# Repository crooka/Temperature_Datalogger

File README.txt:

Reach out to andrew.crook@usu.edu with any questions. 

Use 1 Oz copper
Green soldermask preferred

Most parts have links to both Digikey and JLCPCB. JLCPCB is the preferred supplier, but the big capacitors will need to come from digikey. 
UPDATE: due to cost, I'm only getting the top side assembled, and I'm not getting the ESP32 put on because that will drive up cost. Planning to put the ESP32 with solder paste and the reflow oven at work, and hand solder the back side. 

This section is so I can keep track of what's for what. 
Component purpose/notes:

R11,R12: 	Tell usb to send over 5V
C11,C13,C14,C15:Clean up power to sensors and some ESD protection
C7,C3,C6,C5: 	Clean up power from AMS1117
AMS1117: 	Linear voltage regulator to convert 5V to 3.3V (This is isn't as efficient as a buck converter)
D1: 		Probably not necessary, but this is back current protection. It was in the example. 
R5,R8:		Pull up resistors for the buttons

ESP32: 		This is the brains. Pushing the enable button should reset the board, The IO0 button should make it enter boot mode. 

TMP117: Maybe add in a zero ohm resistor option later so gpio16 can be used for either temperature interrupts or broken out for general IO depending on the assembly? 
	Verify that tying ADD0 to GND gives I2C address 0x48.
	Using recommended 4.7Kohm pull up resistor for SDA and SCL. One source said 2.2K may be better?  

BH1750: Tie ADDR to GND for I2C address 0x23

BME280 Tie CSB to VDDIO for I2C (tie to GND for SPI) With I2C selected, tie SDO to GND for I2C address 0x76

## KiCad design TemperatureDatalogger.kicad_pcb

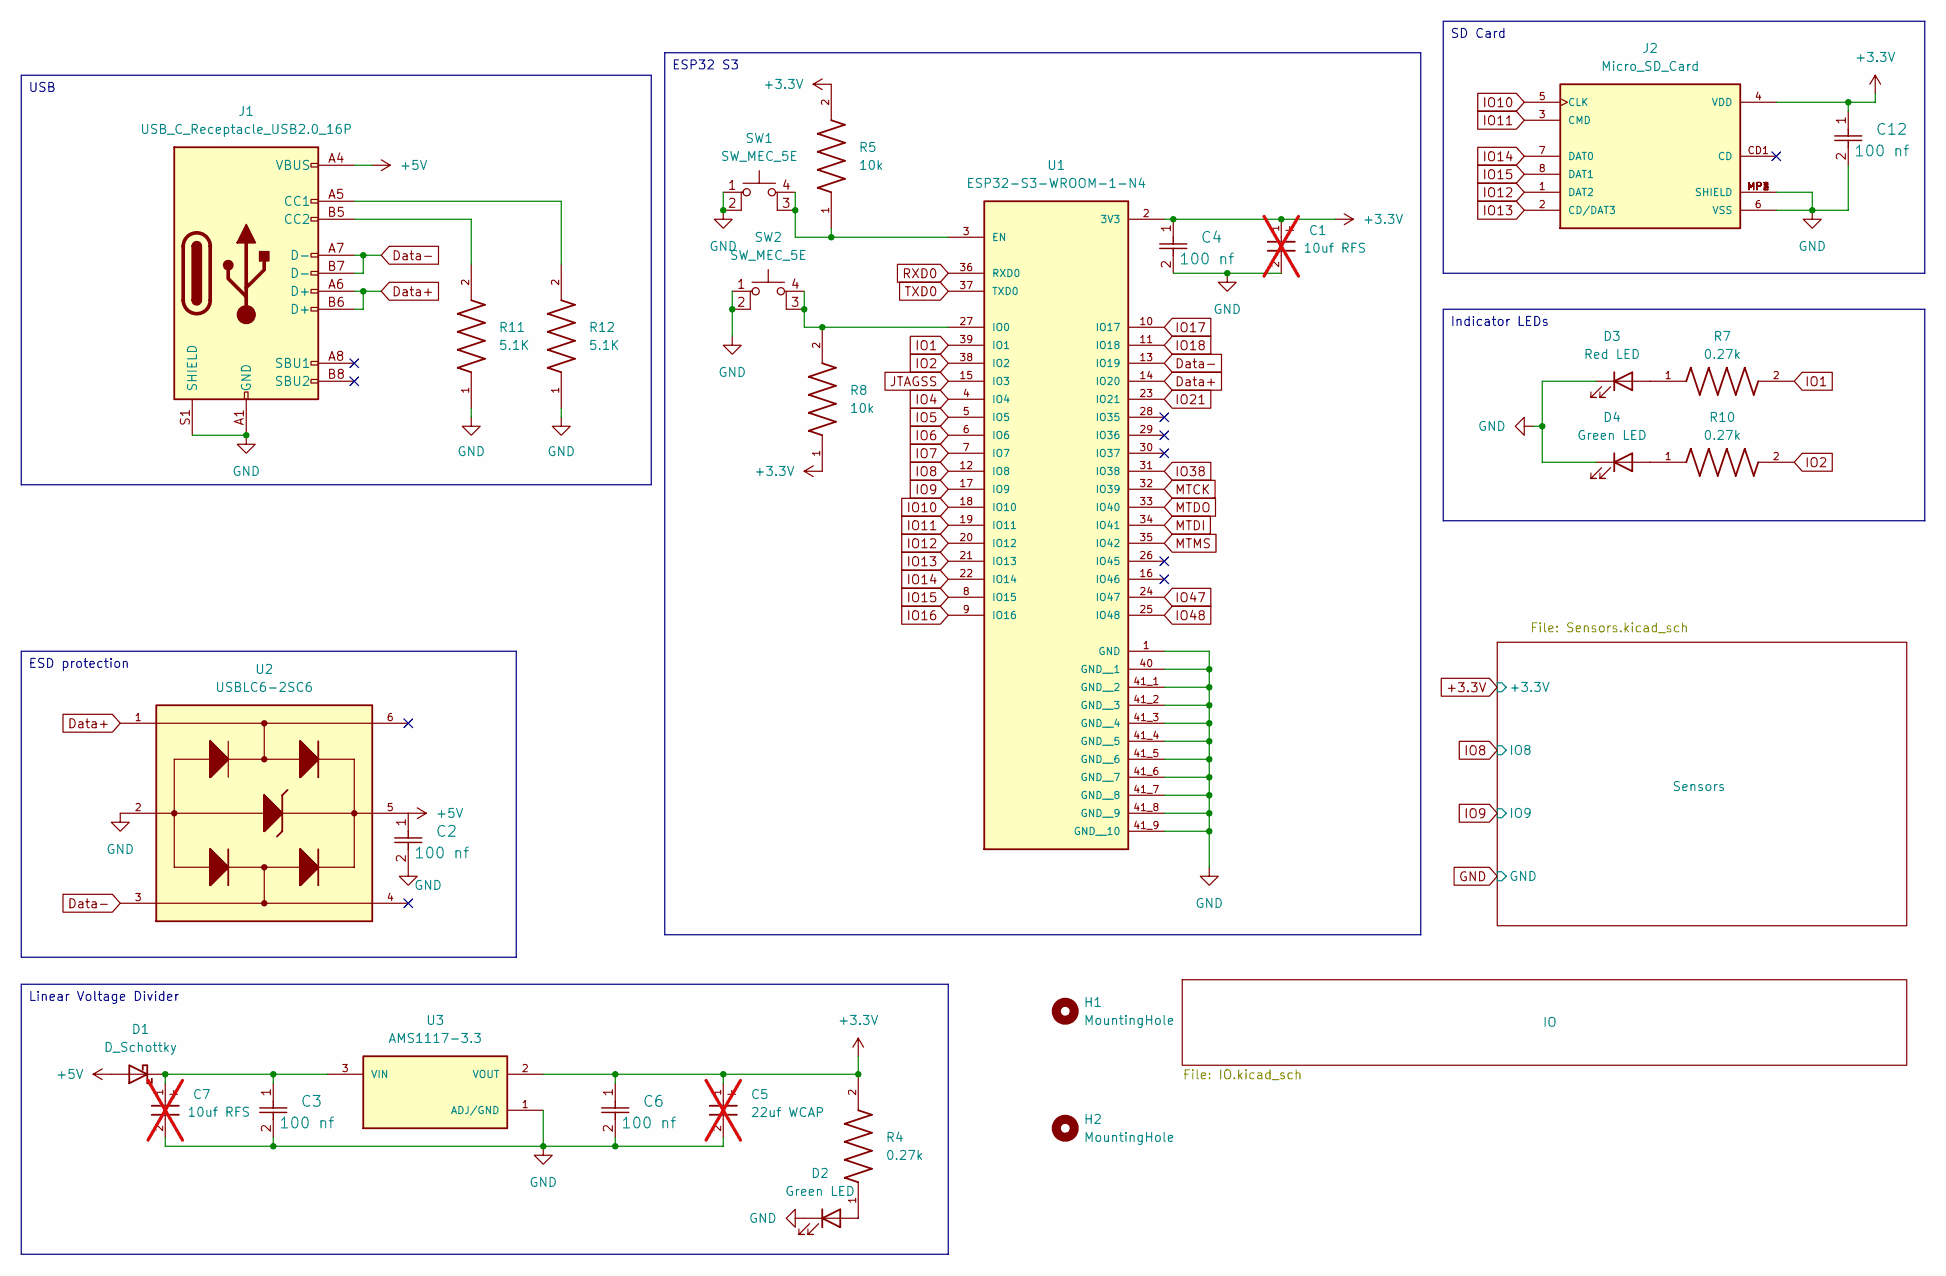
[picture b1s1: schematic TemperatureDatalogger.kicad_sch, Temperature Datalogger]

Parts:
C1, C7: 10uf RFS; RF-A_NCH-M; MPN RFS1A100MCN1GB; not fitted
C2, C3, C4, C6, C12: 100 nf; CAP_CC0603KRX5R8BB104_YAG-M; MPN CC0603KRX5R8BB104
C5: 22uf WCAP; WCAP-PSLP_4X5.5_DXL_; MPN 875105240003; not fitted
D1: D_Schottky; DO-214AC_VIS-M; MPN BYS10-25-E3/TR
D2, D4: Green LED; LED_0604_SMD; MPN 150060VS55040
D3: Red LED; LED_0604_SMD; MPN 150060RS75000
H1, H2: MountingHole; MountingHole_2.7mm_M2.5_ISO14580
J1: USB_C_Receptacle_USB2.0_16P; USB_C_Receptacle_HRO_TYPE-C-31-M-12; MPN TYPE-C-31-M-12
J2: Micro_SD_Card; TF-01A; MPN TF-01A
R4, R7, R10: 0.27k; RES_ERJPA3F2700V; MPN RC0603FR-13270RL
R5, R8: 10k; RES_ERJPA3F2700V; MPN RC0603FR-0710KL
R11, R12: 5.1K; RES_ERJPA3F2700V; MPN RC0603FR-075K1L
SW1, SW2: SW_MEC_5E; button; MPN B3SN-3012P
U1: ESP32-S3-WROOM-1-N4; XCVR_ESP32-S3-WROOM-1-N4; PARTREV v1.0
U2: USBLC6-2SC6; SOT95P280X145-6N; MPN USBLC6-2SC6
U3: AMS1117-3.3; SOT229P700X180-4N; PARTREV NA

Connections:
+3.3V: C1.1, C4.1, C5.1, C6.1, C12.1, J2.4 (VDD), R4.2, R5.2, R8.1, U1.2 (3V3), U3.2 (VOUT); also elsewhere on the board
+5V: C2.1, D1.2 (A), J1.A4 (VBUS), J1.A9 (VBUS), J1.B4 (VBUS), J1.B9 (VBUS), U2.5; also elsewhere on the board
Data+: J1.A6 (D+), J1.B6 (D+), U1.14 (IO20), U2.1
Data-: J1.A7 (D-), J1.B7 (D-), U1.13 (IO19), U2.3
GND: C1.2, C2.2, C3.2, C4.2, C5.2, C6.2, C7.2, C12.2, D2.1 (K), D3.1 (K), D4.1 (K), J1.A1 (GND), J1.A12 (GND), J1.B1 (GND), J1.B12 (GND), J1.S1 (SHIELD), J2.6 (VSS), J2.MP1 (SHIELD), J2.MP2 (SHIELD), J2.MP3 (SHIELD), J2.MP4 (SHIELD), R11.1, R12.1, SW1.1, SW1.2, SW2.1, SW2.2, U1.1 (GND), U1.40 (GND__1), U1.41_1 (GND__2), U1.41_2 (GND__3), U1.41_3 (GND__4), U1.41_4 (GND__5), U1.41_5 (GND__6), U1.41_6 (GND__7), U1.41_7 (GND__8), U1.41_8 (GND__9), U1.41_9 (GND__10), U1.41_10, U1.41_11, U1.41_12, U1.41_13, U1.41_14, U1.41_15, U1.41_16, U1.41_17, U1.41_18, U1.41_19, U1.41_20, U1.41_21, U2.2, U3.1 (ADJ/GND); also elsewhere on the board
IO1: R7.2, U1.39 (IO1)
IO2: R10.2, U1.38 (IO2)
IO4: U1.4 (IO4); also elsewhere on the board
IO5: U1.5 (IO5); also elsewhere on the board
IO6: U1.6 (IO6); also elsewhere on the board
IO7: U1.7 (IO7); also elsewhere on the board
IO8: U1.12 (IO8); also elsewhere on the board
IO9: U1.17 (IO9); also elsewhere on the board
IO10: J2.5 (CLK), U1.18 (IO10)
IO11: J2.3 (CMD), U1.19 (IO11)
IO12: J2.1 (DAT2), U1.20 (IO12)
IO13: J2.2 (CD/DAT3), U1.21 (IO13)
IO14: J2.7 (DAT0), U1.22 (IO14)
IO15: J2.8 (DAT1), U1.8 (IO15)
IO16: U1.9 (IO16); also elsewhere on the board
IO17: U1.10 (IO17); also elsewhere on the board
IO18: U1.11 (IO18); also elsewhere on the board
IO21: U1.23 (IO21); also elsewhere on the board
IO38: U1.31 (IO38); also elsewhere on the board
IO47: U1.24 (IO47); also elsewhere on the board
IO48: U1.25 (IO48); also elsewhere on the board
JTAGSS: U1.15 (IO3); also elsewhere on the board
MTCK: U1.32 (IO39); also elsewhere on the board
MTDI: U1.34 (IO41); also elsewhere on the board
MTDO: U1.33 (IO40); also elsewhere on the board
MTMS: U1.35 (IO42); also elsewhere on the board
unnamed: C3.1, C7.1, D1.1 (K), U3.3 (VIN)
unnamed: D2.2 (A), R4.1
unnamed: D3.2 (A), R7.1
unnamed: D4.2 (A), R10.1
unnamed: J1.A5 (CC1), R12.2
unnamed: J1.B5 (CC2), R11.2
unnamed: R5.1, SW1.3 (K), SW1.4 (A), U1.3 (EN)
unnamed: R8.2, SW2.3 (K), SW2.4 (A), U1.27 (IO0)
RXD0: U1.36 (RXD0); also elsewhere on the board
TXD0: U1.37 (TXD0); also elsewhere on the board

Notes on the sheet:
USB
ESP32 S3
Linear Voltage Divider
SD Card
ESD protection
Indicator LEDs

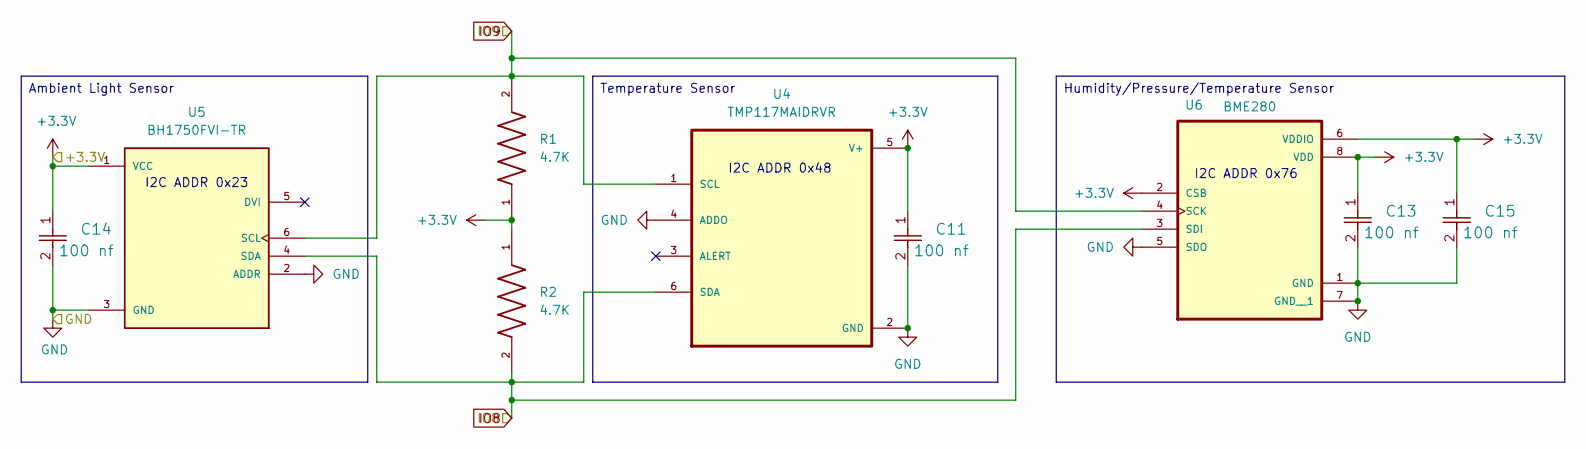
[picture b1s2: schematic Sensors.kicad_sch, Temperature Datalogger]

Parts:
C11, C13, C14, C15: 100 nf; CAP_CC0603KRX5R8BB104_YAG-M; MPN CC0603KRX5R8BB104
R1, R2: 4.7K; RES_ERJPA3F2700V; MPN RC0603FR-074K7L
U4: TMP117MAIDRVR; SON65P200X200X80-7N; MPN TMP117MAIDRVR
U5: BH1750FVI-TR; XDCR_BH1750FVI-TR; PARTREV D
U6: BME280; PSON65P250X250X100-8N; MPN BME280

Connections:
+3.3V: C11.1, C13.1, C14.1, C15.1, R1.1, R2.1, U4.5 (V+), U5.1 (VCC), U6.2 (CSB), U6.6 (VDDIO), U6.8 (VDD); also elsewhere on the board
GND: C11.2, C13.2, C14.2, C15.2, U4.2 (GND), U4.4 (ADDO), U4.7, U5.2 (ADDR), U5.3 (GND), U6.1 (GND), U6.5 (SDO), U6.7 (GND__1); also elsewhere on the board
IO8: R2.2, U4.6 (SDA), U5.4 (SDA), U6.3 (SDI); also elsewhere on the board
IO9: R1.2, U4.1 (SCL), U5.6 (SCL), U6.4 (SCK); also elsewhere on the board

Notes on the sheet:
I2C ADDR 0x23
I2C ADDR 0x48
I2C ADDR 0x76
Temperature Sensor
Ambient Light Sensor
Humidity/Pressure/Temperature Sensor

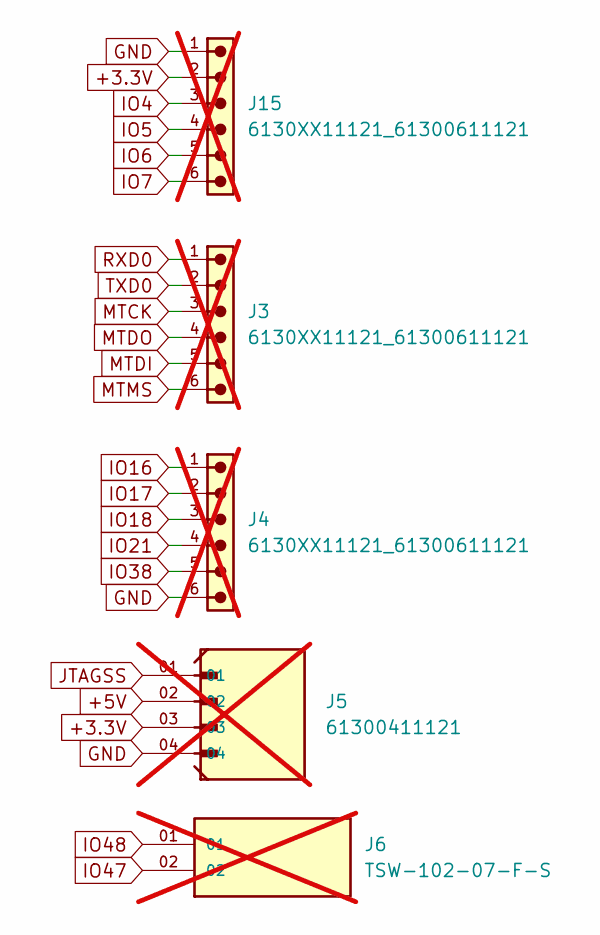
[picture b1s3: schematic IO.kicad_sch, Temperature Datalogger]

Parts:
J3, J4, J15: 6130XX11121_61300611121; 61300611121; not fitted
J5: 61300411121; WURTH_61300411121; not fitted
J6: TSW-102-07-F-S; SAMTEC_TSW-102-07-F-S; PARTREV R; not fitted

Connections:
+3.3V: J5.03, J15.2; also elsewhere on the board
+5V: J5.02; also elsewhere on the board
GND: J4.6, J5.04, J15.1; also elsewhere on the board
IO4: J15.3; also elsewhere on the board
IO5: J15.4; also elsewhere on the board
IO6: J15.5; also elsewhere on the board
IO7: J15.6; also elsewhere on the board
IO16: J4.1; also elsewhere on the board
IO17: J4.2; also elsewhere on the board
IO18: J4.3; also elsewhere on the board
IO21: J4.4; also elsewhere on the board
IO38: J4.5; also elsewhere on the board
IO47: J6.02; also elsewhere on the board
IO48: J6.01; also elsewhere on the board
JTAGSS: J5.01; also elsewhere on the board
MTCK: J3.3; also elsewhere on the board
MTDI: J3.5; also elsewhere on the board
MTDO: J3.4; also elsewhere on the board
MTMS: J3.6; also elsewhere on the board
RXD0: J3.1; also elsewhere on the board
TXD0: J3.2; also elsewhere on the board

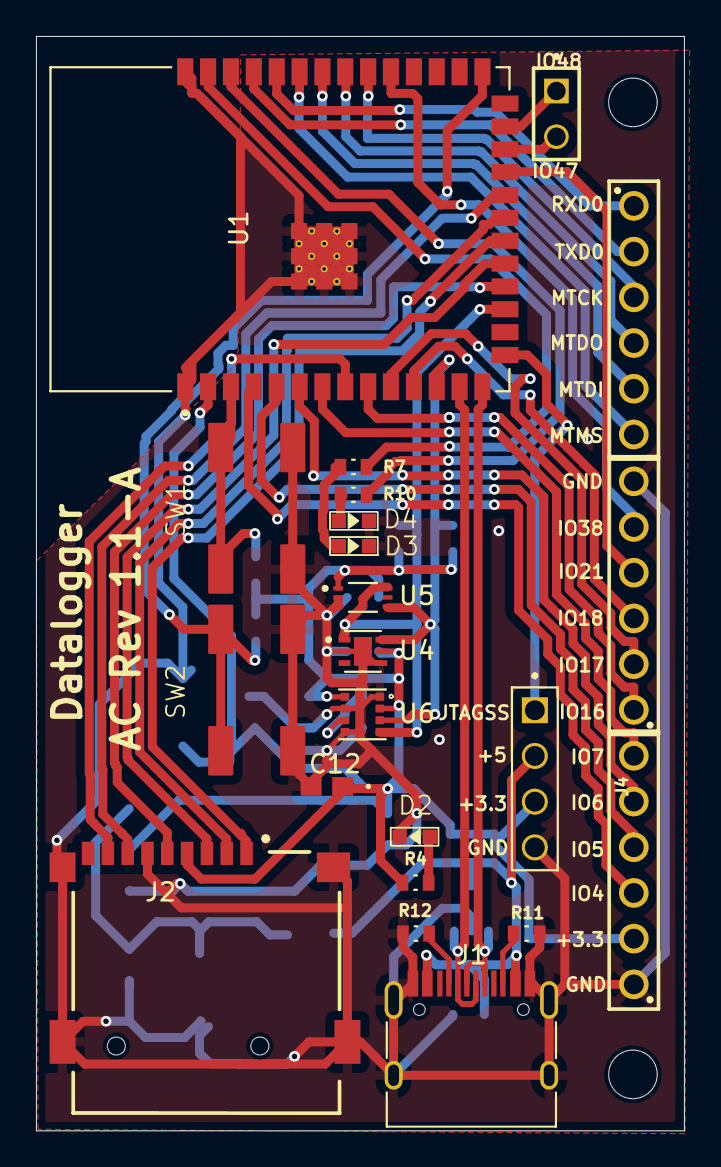
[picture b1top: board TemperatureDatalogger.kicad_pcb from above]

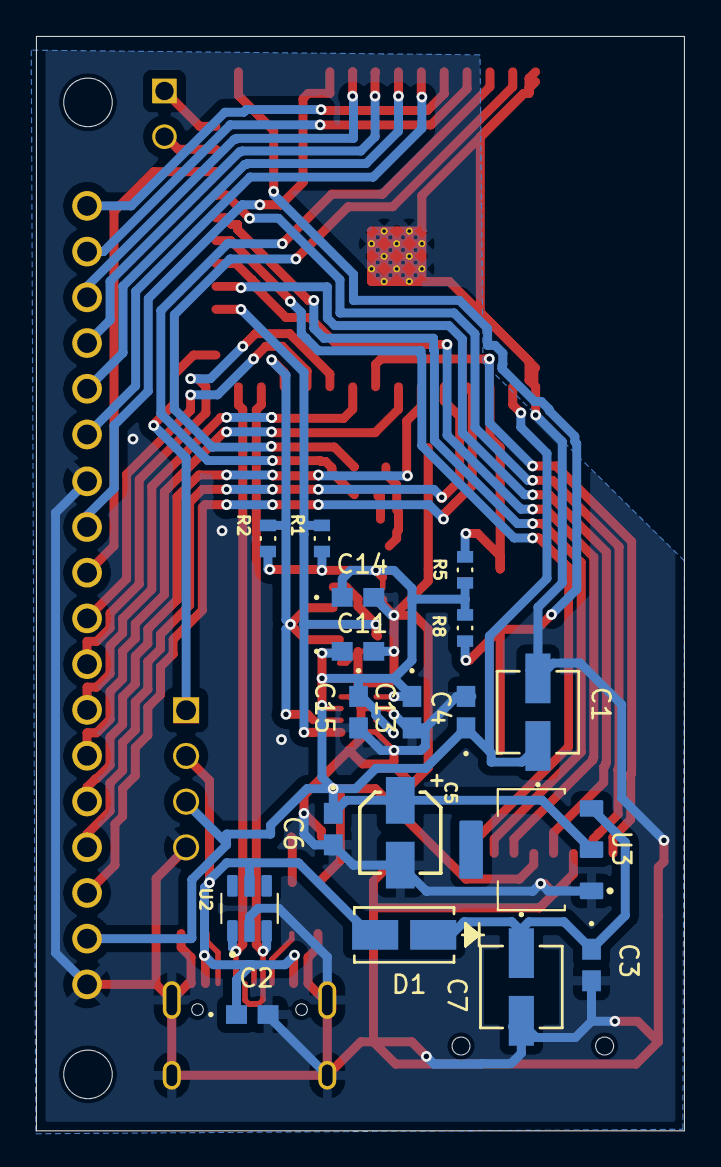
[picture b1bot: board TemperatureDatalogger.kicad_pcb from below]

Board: 2 copper layers, 36.0 x 60.8 mm, 42 parts (18 on the bottom side), 41 nets.
